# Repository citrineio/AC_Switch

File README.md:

# AC_Switch
ESP32 based AC load controller with relay and AC/DC power supply

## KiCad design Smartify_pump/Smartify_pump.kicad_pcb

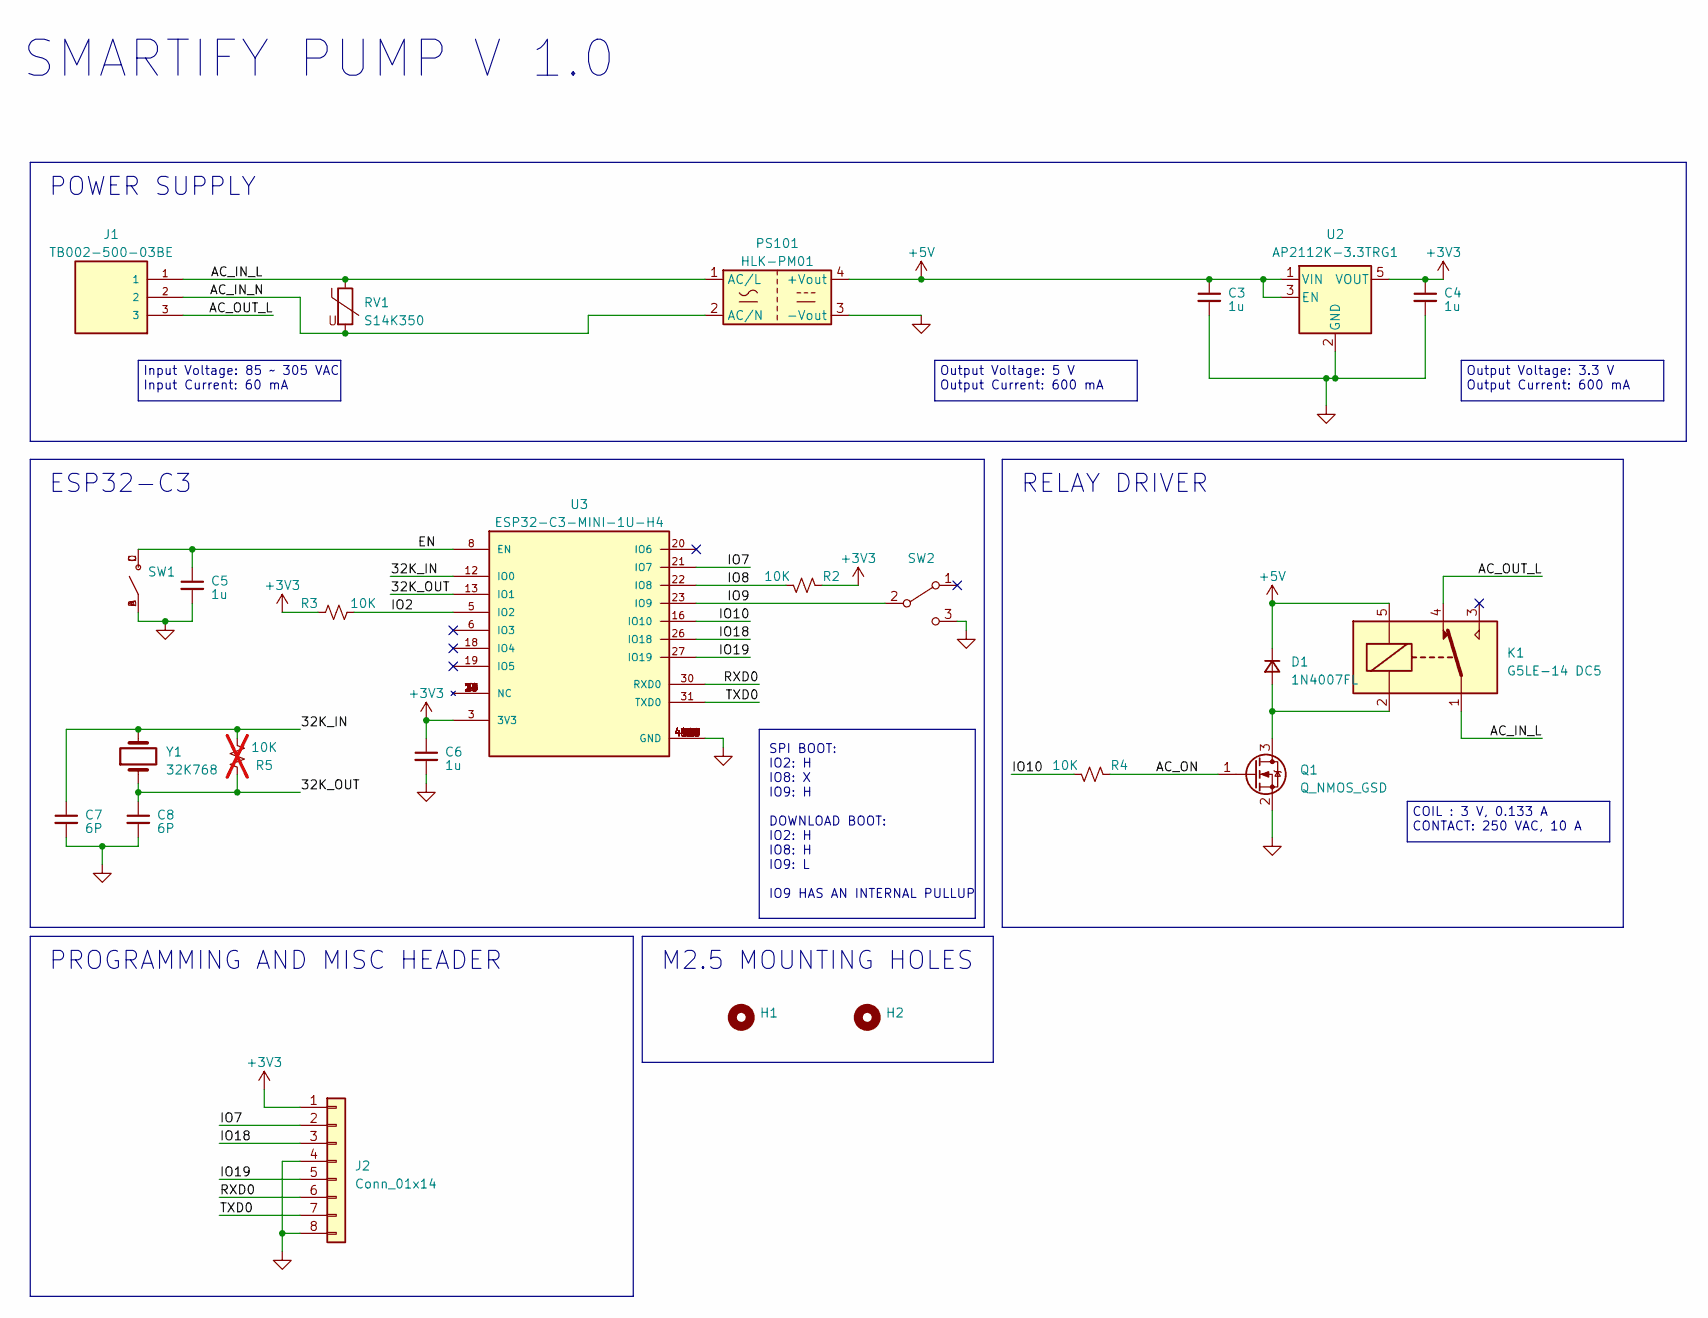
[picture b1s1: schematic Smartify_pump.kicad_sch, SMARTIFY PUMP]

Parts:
C3, C4, C5, C6: 1u; CAPC1608X90N_SAMSUNG; Part Number CL10B105KO8NNNC
C7, C8: 6P; CAPC1608X90N_SAMSUNG; Part Number CL10C060DB8NNNC
D1: 1N4007FL; CR_SOD-123FL_SME; Part Number 1N4007FL
H1, H2: MountingHole; MountingHole_2.7mm_M2.5
J1: TB002-500-03BE; CUI_TB002-500-03BE; Part Number TB002-500-03BE
J2: Conn_01x14; PinHeader_1x08_P2.54mm_Vertical; Part Number PPTC141LFBN-RC
K1: G5LE-14 DC5; Relay_SPDT_Omron-G5LE-1; Part Number G5LE-14 DC5
PS101: HLK-PM01; Converter_ACDC_HiLink_HLK-PMxx; Part Number HLK-PM01
Q1: Q_NMOS_GSD; DMN65D8L-7_MOSFET; Part Number DMN65D8L-7
R2, R3, R4: 10K; RESC1607X60N; Part Number RC0603JR-0710KL
R5: 10K; RESC1607X60N; Part Number RC0603JR-0710KL; not fitted
RV1: S14K350; VARS_B72214S_15P5X5P6-7P5-2P2_TDK; Part Number B72214S0351K101
SW1: TS-1187A-B-A-B; SW_TS-1187A-B-A-B; Part Number TS-1187A-B-A-B
SW2: SW_SPDT; SW_JS102011SAQN; Part Number JS102011SAQN
U2: AP2112K-3.3TRG1; SOT-23-5; Part Number AP2112K-3.3TRG1
U3: ESP32-C3-MINI-1U-H4; XCVR_ESP32-C3-MINI-1U-N4; Part Number ESP32-C3-MINI-1U-H4
Y1: 32K768; XTAL_FC-135R_32.7680KA-AG0; Part Number FC-135R 32.7680KA-AG0

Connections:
+3V3: C4.1, C6.1, J2.1, R2.1, R3.1, U2.5 (VOUT), U3.3 (3V3)
+5V: C3.1, D1.1 (K), K1.5, PS101.4 (+Vout), U2.1 (VIN), U2.3 (EN)
/32K_IN: C7.1, R5.2, U3.12 (IO0), Y1.2
/32K_OUT: C8.1, R5.1, U3.13 (IO1), Y1.1
/AC_IN_L: J1.1, K1.1, PS101.1 (AC/L), RV1.1
/AC_IN_N: J1.2, PS101.2 (AC/N), RV1.2
/AC_ON: Q1.1 (G), R4.1
/AC_OUT_L: J1.3, K1.4
/EN: C5.1, SW1.C, SW1.D, U3.8 (EN)
/IO2: R3.2, U3.5 (IO2)
/IO7: J2.2, U3.21 (IO7)
/IO8: R2.2, U3.22 (IO8)
/IO9: SW2.2 (B), U3.23 (IO9)
/IO10: R4.2, U3.16 (IO10)
/IO18: J2.3, U3.26 (IO18)
/IO19: J2.5, U3.27 (IO19)
/RXD0: J2.6, U3.30 (RXD0)
/TXD0: J2.7, U3.31 (TXD0)
GND: C3.2, C4.2, C5.2, C6.2, C7.2, C8.2, J2.4, J2.8, PS101.3 (-Vout), Q1.2 (S), SW1.A, SW1.B, SW2.3 (C), U2.2 (GND), U3.1 (GND), U3.2 (GND), U3.11 (GND), U3.14 (GND), U3.36 (GND), U3.37 (GND), U3.38 (GND), U3.39 (GND), U3.40 (GND), U3.41 (GND), U3.42 (GND), U3.43 (GND), U3.44 (GND), U3.45 (GND), U3.46 (GND), U3.47 (GND), U3.48 (GND), U3.49_1 (GND), U3.49_2 (GND), U3.49_3 (GND), U3.49_4 (GND), U3.49_5 (GND), U3.49_6 (GND), U3.49_7 (GND), U3.49_8 (GND), U3.49_9 (GND), U3.50 (GND), U3.51 (GND), U3.52 (GND), U3.53 (GND)
unnamed: D1.2 (A), K1.2, Q1.3 (D)

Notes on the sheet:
M2.5 MOUNTING HOLES
V 1.0
Output Voltage: 5 V Output Current: 600 mA
ESP32-C3
COIL : 3 V, 0.133 A CONTACT: 250 VAC, 10 A
Output Voltage: 3.3 V Output Current: 600 mA
POWER SUPPLY
SPI BOOT: IO2: H IO8: X IO9: H DOWNLOAD BOOT: IO2: H IO8: H IO9: L IO9 HAS AN INTERNAL PULLUP
RELAY DRIVER
Input Voltage: 85 ~ 305 VAC Input Current: 60 mA
SMARTIFY PUMP
PROGRAMMING AND MISC HEADER

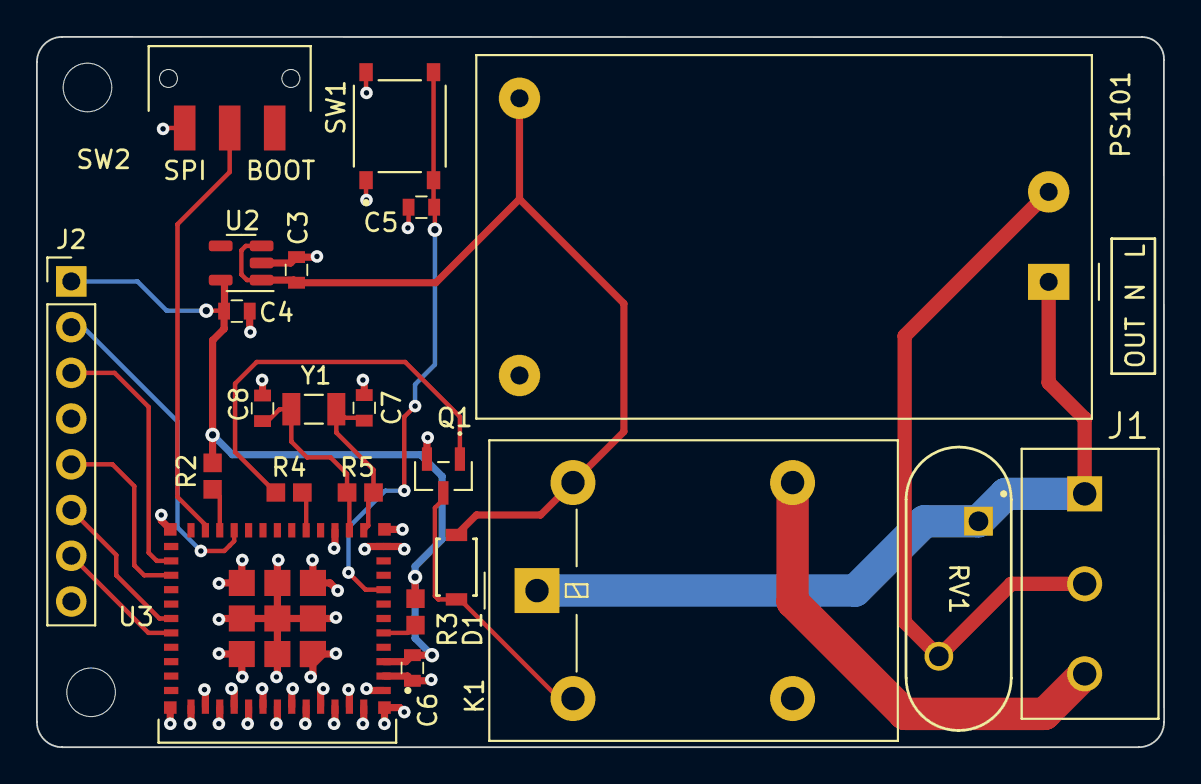
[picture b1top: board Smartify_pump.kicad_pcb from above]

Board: 4 copper layers, 62.6 x 39.5 mm, 24 parts (0 on the bottom side), 20 nets.
